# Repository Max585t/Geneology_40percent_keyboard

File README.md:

BOM
|Item|amount|link|price total|
|----|------|----|-----------|
|gateron lunar probe switches|57|https://milktooth.com/products/switches/lunar-probe|$25.14|
|1N4148 SOD-123 diodes|57|https://www.adafruit.com/product/5099|$4.95|
|3 pin magnetic connector|2|https://www.adafruit.com/product/5360|$11.9|
|5 pin magnetic connector|2|https://www.adafruit.com/product/5359|$13.9|
|rp2040-tiny with usb adapter|1|https://www.waveshare.com/rp2040-tiny.htm?sku=24665|$4.99|
|skuf feet|6|https://keeb.io/products/skuf-silicone-rubber-keyboard-feet|$2.99|
|PCB|1|jlcpcb.com|$19.2|
|Total|not including shipping|not including taxes|$83.07|

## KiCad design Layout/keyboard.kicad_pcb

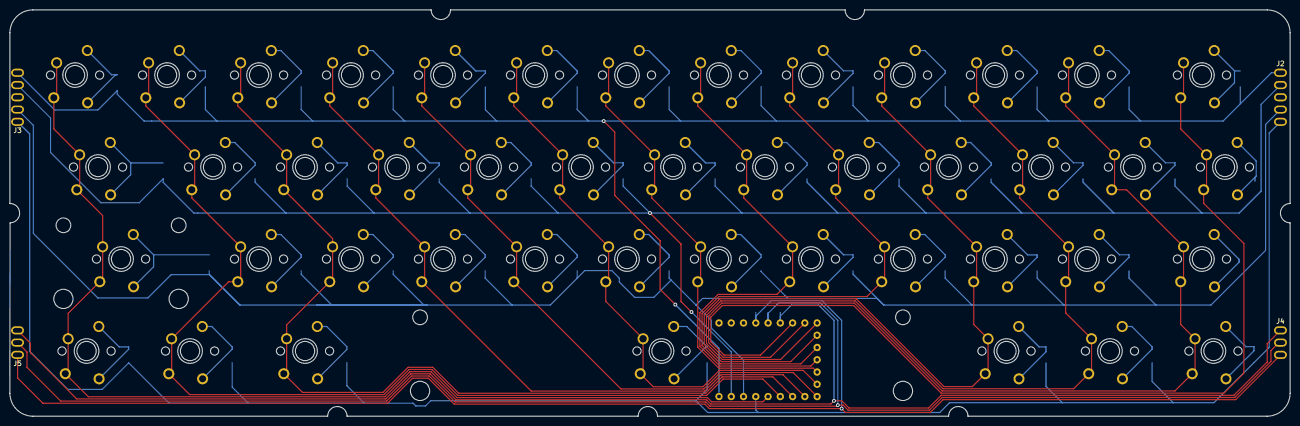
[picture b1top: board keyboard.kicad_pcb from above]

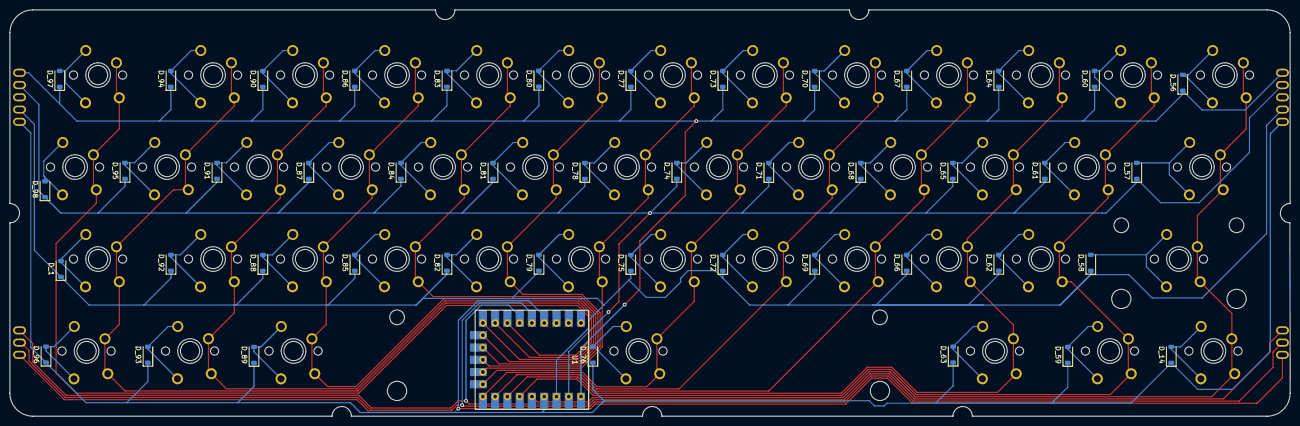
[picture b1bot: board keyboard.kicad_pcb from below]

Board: 2 copper layers, 265.1 x 84.1 mm, 140 parts (46 on the bottom side), 65 nets.

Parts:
D_1, D_14, D_56, D_57, D_58, D_59, D_60, D_61, D_62, D_63, D_64, D_65, D_66, D_67, D_68, D_69, D_70, D_71, D_72, D_73, D_74, D_75, D_76, D_77, D_78, D_79, D_80, D_81, D_82, D_83, D_84, D_85, D_86, D_87, D_88, D_89, D_90, D_91, D_92, D_93, D_94, D_95, D_96, D_97, D_98: D; D_SOD-123
J2, J3: Conn_01x04_Socket; PinHeader_1x05_P2.54mm_Horizontal
J4, J5: Conn_01x03_Socket; PinHeader_1x03_P2.54mm_Horizontal
K_1, K_94, K_100, K_134: KEYSW; MX-Solderable-1.5U
K_14, K_17, K_18, K_19, K_20, K_22, K_23, K_24, K_25, K_26, K_27, K_28, K_29, K_30, K_31, K_32, K_33, K_35, K_36, K_37, K_38, K_39, K_40, K_41, K_42, K_43, K_44, K_45, K_46, K_48, K_49, K_50, K_51, K_52, K_53, K_57: KEYSW; Gateron-KS33-Solderable-1U
K_15, K_21, K_54, K_56: KEYSW; Gateron-KS33-Solderable-1.5U
K_16: KEYSW; Gateron-KS33-Solderable-2U
K_34: KEYSW; Gateron-KS33-Solderable-6.25U
K_47, K_55, K_71: KEYSW; Gateron-KS33-Solderable-1.25U
K_70, K_126, K_133: KEYSW; MX-Solderable-1.25U
K_93, K_96, K_97, K_98, K_99, K_101, K_102, K_103, K_104, K_105, K_106, K_107, K_108, K_109, K_110, K_111, K_112, K_114, K_115, K_116, K_117, K_118, K_119, K_120, K_121, K_122, K_123, K_124, K_125, K_127, K_128, K_129, K_130, K_131, K_132, K_135: KEYSW; MX-Solderable-1U
K_95: KEYSW; MX-Solderable-2U
K_113: KEYSW; MX-Solderable-6.25U
U1: Waveshare_rp2040_Tiny

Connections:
unnamed: D_1.2 (A), K_1.2 (ROW), K_54.2 (ROW)
unnamed: D_14.2 (A), K_70.2 (ROW), K_71.2 (ROW)
unnamed: D_56.2 (A), K_14.2 (ROW), K_93.2 (ROW)
unnamed: D_57.2 (A), K_15.2 (ROW), K_94.2 (ROW)
unnamed: D_58.2 (A), K_16.2 (ROW), K_95.2 (ROW)
unnamed: D_59.2 (A), K_17.2 (ROW), K_96.2 (ROW)
unnamed: D_60.2 (A), K_18.2 (ROW), K_97.2 (ROW)
unnamed: D_61.2 (A), K_19.2 (ROW), K_98.2 (ROW)
unnamed: D_62.2 (A), K_20.2 (ROW), K_99.2 (ROW)
unnamed: D_63.2 (A), K_21.2 (ROW), K_100.2 (ROW)
unnamed: D_64.2 (A), K_22.2 (ROW), K_101.2 (ROW)
unnamed: D_65.2 (A), K_23.2 (ROW), K_102.2 (ROW)
unnamed: D_66.2 (A), K_24.2 (ROW), K_103.2 (ROW)
unnamed: D_67.2 (A), K_25.2 (ROW), K_104.2 (ROW)
unnamed: D_68.2 (A), K_26.2 (ROW), K_105.2 (ROW)
unnamed: D_69.2 (A), K_27.2 (ROW), K_106.2 (ROW)
unnamed: D_70.2 (A), K_28.2 (ROW), K_107.2 (ROW)
unnamed: D_71.2 (A), K_29.2 (ROW), K_108.2 (ROW)
unnamed: D_72.2 (A), K_30.2 (ROW), K_109.2 (ROW)
unnamed: D_73.2 (A), K_31.2 (ROW), K_110.2 (ROW)
unnamed: D_74.2 (A), K_32.2 (ROW), K_111.2 (ROW)
unnamed: D_75.2 (A), K_33.2 (ROW), K_112.2 (ROW)
unnamed: D_76.2 (A), K_34.2 (ROW), K_113.2 (ROW)
unnamed: D_77.2 (A), K_35.2 (ROW), K_114.2 (ROW)
unnamed: D_78.2 (A), K_36.2 (ROW), K_115.2 (ROW)
unnamed: D_79.2 (A), K_37.2 (ROW), K_116.2 (ROW)
unnamed: D_80.2 (A), K_38.2 (ROW), K_117.2 (ROW)
unnamed: D_81.2 (A), K_39.2 (ROW), K_118.2 (ROW)
unnamed: D_82.2 (A), K_40.2 (ROW), K_119.2 (ROW)
unnamed: D_83.2 (A), K_41.2 (ROW), K_120.2 (ROW)
unnamed: D_84.2 (A), K_42.2 (ROW), K_121.2 (ROW)
unnamed: D_85.2 (A), K_43.2 (ROW), K_122.2 (ROW)
unnamed: D_86.2 (A), K_44.2 (ROW), K_123.2 (ROW)
unnamed: D_87.2 (A), K_45.2 (ROW), K_124.2 (ROW)
unnamed: D_88.2 (A), K_46.2 (ROW), K_125.2 (ROW)
unnamed: D_89.2 (A), K_47.2 (ROW), K_126.2 (ROW)
unnamed: D_90.2 (A), K_48.2 (ROW), K_127.2 (ROW)
unnamed: D_91.2 (A), K_49.2 (ROW), K_128.2 (ROW)
unnamed: D_92.2 (A), K_50.2 (ROW), K_129.2 (ROW)
unnamed: D_93.2 (A), K_51.2 (ROW), K_130.2 (ROW)
unnamed: D_94.2 (A), K_52.2 (ROW), K_131.2 (ROW)
unnamed: D_95.2 (A), K_53.2 (ROW), K_132.2 (ROW)
unnamed: D_96.2 (A), K_55.2 (ROW), K_133.2 (ROW)
unnamed: D_97.2 (A), K_56.2 (ROW), K_134.2 (ROW)
unnamed: D_98.2 (A), K_57.2 (ROW), K_135.2 (ROW)
col0: K_14.1 (COL), K_15.1 (COL), K_16.1 (COL), K_70.1 (COL), K_71.1 (COL), K_93.1 (COL), K_94.1 (COL), K_95.1 (COL), U1.4 (GP04)
col1: K_17.1 (COL), K_18.1 (COL), K_19.1 (COL), K_20.1 (COL), K_96.1 (COL), K_97.1 (COL), K_98.1 (COL), K_99.1 (COL), U1.5 (GP05)
col2: K_21.1 (COL), K_22.1 (COL), K_23.1 (COL), K_24.1 (COL), K_100.1 (COL), K_101.1 (COL), K_102.1 (COL), K_103.1 (COL), U1.6 (GP06)
col3: K_25.1 (COL), K_26.1 (COL), K_27.1 (COL), K_104.1 (COL), K_105.1 (COL), K_106.1 (COL), U1.7 (GP07)
col4: K_28.1 (COL), K_29.1 (COL), K_30.1 (COL), K_107.1 (COL), K_108.1 (COL), K_109.1 (COL), U1.8 (GP08)
col5: K_31.1 (COL), K_32.1 (COL), K_33.1 (COL), K_34.1 (COL), K_110.1 (COL), K_111.1 (COL), K_112.1 (COL), K_113.1 (COL), U1.9 (GP09)
col6: K_35.1 (COL), K_36.1 (COL), K_37.1 (COL), K_114.1 (COL), K_115.1 (COL), K_116.1 (COL), U1.10 (GP10)
col7: K_38.1 (COL), K_39.1 (COL), K_40.1 (COL), K_117.1 (COL), K_118.1 (COL), K_119.1 (COL), U1.11 (GP11)
col8: K_41.1 (COL), K_42.1 (COL), K_43.1 (COL), K_120.1 (COL), K_121.1 (COL), K_122.1 (COL), U1.12 (GP12)
col9: K_44.1 (COL), K_45.1 (COL), K_46.1 (COL), K_47.1 (COL), K_123.1 (COL), K_124.1 (COL), K_125.1 (COL), K_126.1 (COL), U1.13 (GP13)
col10: K_48.1 (COL), K_49.1 (COL), K_50.1 (COL), K_51.1 (COL), K_127.1 (COL), K_128.1 (COL), K_129.1 (COL), K_130.1 (COL), U1.14 (GP14)
col11: K_1.1 (COL), K_52.1 (COL), K_53.1 (COL), K_54.1 (COL), K_55.1 (COL), K_131.1 (COL), K_132.1 (COL), K_133.1 (COL), U1.15 (GP15)
col12: K_56.1 (COL), K_57.1 (COL), K_134.1 (COL), K_135.1 (COL), U1.16 (GP26)
col13: J4.1, J5.3, U1.17 (GP27)
col14: J4.2, J5.2, U1.18 (GP28)
col15: J4.3, J5.1, U1.19 (GP29)
row0: D_56.1 (K), D_60.1 (K), D_64.1 (K), D_67.1 (K), D_70.1 (K), D_73.1 (K), D_77.1 (K), D_80.1 (K), D_83.1 (K), D_86.1 (K), D_90.1 (K), D_94.1 (K), D_97.1 (K), J2.1, J3.5, U1.0 (GP00)
row1: D_57.1 (K), D_61.1 (K), D_65.1 (K), D_68.1 (K), D_71.1 (K), D_74.1 (K), D_78.1 (K), D_81.1 (K), D_84.1 (K), D_87.1 (K), D_91.1 (K), D_95.1 (K), D_98.1 (K), J2.2, J3.4, U1.1 (GP01)
row2: D_1.1 (K), D_58.1 (K), D_62.1 (K), D_66.1 (K), D_69.1 (K), D_72.1 (K), D_75.1 (K), D_79.1 (K), D_82.1 (K), D_85.1 (K), D_88.1 (K), D_92.1 (K), J2.4, J3.2, U1.2 (GP02)
row3: D_14.1 (K), D_59.1 (K), D_63.1 (K), D_76.1 (K), D_89.1 (K), D_93.1 (K), D_96.1 (K), J2.5, J3.1, U1.3 (GP03)

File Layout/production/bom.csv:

Designator,Footprint,Quantity,Value,LCSC Part #
"D_1, D_14, D_56, D_57, D_58, D_59, D_60, D_61, D_62, D_63, D_64, D_65, D_66, D_67, D_68, D_69, D_70, D_71, D_72, D_73, D_74, D_75, D_76, D_77, D_78, D_79, D_80, D_81, D_82, D_83, D_84, D_85, D_86, D_87, D_88, D_89, D_90, D_91, D_92, D_93, D_94, D_95, D_96, D_97, D_98",D_SOD-123,45,D,
"J2, J3",PinHeader_1x05_P2.54mm_Horizontal,2,Conn_01x04_Socket,
"J4, J5",PinHeader_1x03_P2.54mm_Horizontal,2,Conn_01x03_Socket,
"K_1, K_100, K_134, K_94",MX-Solderable-1.5U,4,KEYSW,
"K_101, K_102, K_103, K_104, K_105, K_106, K_107, K_108, K_109, K_110, K_111, K_112, K_114, K_115, K_116, K_117, K_118, K_119, K_120, K_121, K_122, K_123, K_124, K_125, K_127, K_128, K_129, K_130, K_131, K_132, K_135, K_93, K_96, K_97, K_98, K_99",MX-Solderable-1U,36,KEYSW,
K_113,MX-Solderable-6.25U,1,KEYSW,
"K_126, K_133, K_70",MX-Solderable-1.25U,3,KEYSW,
"K_14, K_17, K_18, K_19, K_20, K_22, K_23, K_24, K_25, K_26, K_27, K_28, K_29, K_30, K_31, K_32, K_33, K_35, K_36, K_37, K_38, K_39, K_40, K_41, K_42, K_43, K_44, K_45, K_46, K_48, K_49, K_50, K_51, K_52, K_53, K_57",Gateron-KS33-Solderable-1U,36,KEYSW,
"K_15, K_21, K_54, K_56",Gateron-KS33-Solderable-1.5U,4,KEYSW,
K_16,Gateron-KS33-Solderable-2U,1,KEYSW,
K_34,Gateron-KS33-Solderable-6.25U,1,KEYSW,
"K_47, K_55, K_71",Gateron-KS33-Solderable-1.25U,3,KEYSW,
K_95,MX-Solderable-2U,1,KEYSW,
U1,Waveshare_rp2040_Tiny,1,~,

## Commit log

2024-05-09 plate
2024-05-14 Work done
2024-08-22 Finish layout
2024-09-04 Finished
2024-09-06 Gerbers - Need to add my name to silkscreen
2024-09-10 PCB is done, silkscreen still needs to be done
2024-09-10 whoops, missed saving schematic
2024-09-13 gerbers for seperate macropad and keyboard
